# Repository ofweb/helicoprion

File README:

# Helicoprion Keyboard

The Helicoprion Keyboard is a 52-key diodeless, flippable, choc spaced, hotswap, aggressive column staggered, split keyboard powered by Pro Micro pin compatible board, eg a nice!nano or a KB2040.
It does not support wireless controllers, but you can use a nice!nano wired if you want

# Inspiration

* [Sweep](https://github.com/davidphilipbarr/Sweep) The main inspiration is from the ferris sweep I started trying to used I needed more keys.
* [Hillside](https://github.com/mmccoyd/hillside) The very pretty promicro foot print and how to wire it.
* [Torn](https://github.com/rtitmuss/torn) For not be afraid of showing th components and that look can be very sexy.

## Features

* Pro Micro MCU - Many options
* Sweep inspired layout - Ergonomic strong column staggering for short pinkies.
* Extra pinky column - for those not too often used keys.
* Flippable PCBs - Cheaper to order the PCBs
* Hotswap low profile choc switches - Experiment with different key switches with the hotswap sockets.
* Very large thumb cluster - Let your thumb do more of the work.
* Both SMD and THT diodes - Pick if you want the easier to solder or the smaller diodes.

## Bill of Materials (BOM)

Quantity | Item
--- | ---
2 | Helicoprion PCB
2 | Pro Micro pin compatable comtrollers
52 | Kailh choc v1 PG1350 switches
52 | Choc v1 keycaps
2 | TRRS jack PJ-320A (not needed for nice!nano)
1 | 3.5mm TRRS cable (not needed for nice!nano)
52 | Kahli hotswap sockets for choc v1 PG1350
4 | Pin headers (20 pin) or sockets
2 | Reset Button (optional) ALPS SKHLLCA010 or footprint compatible

## External footprints and symbols used

External symbols and footprints are not covered by the LICENSE in this repo.

* [Keebio-Parts.pretty](https://github.com/keebio/Keebio-Parts.pretty) is licensed under the MIT License.
* [keyswitches.pretty](https://github.com/daprice/keyswitches.pretty) is licensed under the Creative Commons Attribution-ShareAlike 4.0 International License.
* [Hillside](https://github.com/mmccoyd/hillside) is licensed under the MIT License.

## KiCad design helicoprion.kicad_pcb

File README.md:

# Helicoprion Keyboard

The Helicoprion Keyboard is a 44-key diodeless, flippable, choc spaced, hotswap, aggressive column staggered, split keyboard powered by Pro Micro pin compatible board, eg a nice!nano or a KB2040.
It does not have battery support, but you can use a nice!nano wired if you want.

I made this after having build and attempted to use a sweep. Tha lack of dedicated modifier keys kept being a problem for me. The normal tucky thumb keys are hard to reach for me so I came up with this that I think feels better.
I don't expect this to by my last iteration on a keyboard so it is made to allow me to recycle the MCU and the switches in a next iteration.

# Testing
If you want to see if this is right for you you can start with printing a paper tester (TODO). If you have access to a 3d-printer you can print the step file(TODO) from the repo and add you switches, this should give you a better indication on if it is right.

# Inspiration

* [Sweep](https://github.com/davidphilipbarr/Sweep) The main inspiration is from the ferris sweep I started trying to used I needed more keys.
* [Hillside](https://github.com/mmccoyd/hillside) The very pretty promicro foot print and how to wire it.
* [Torn](https://github.com/rtitmuss/torn) For not be afraid of showing the components and that it can look very nice.

## Features

* Pro Micro MCU - Many options
* Sweep inspired layout - Ergonomic strong column staggering for short pinkies.
* Flippable PCBs - Cheaper to order the PCBs
* Hotswap low profile choc switches - Experiment with different key switches with the hotswap sockets.
* Very large thumb cluster - Let your thumb do more of the work.
* Both SMD and THT diodes - Pick if you want the easier to solder or the smaller diodes.

## Bill of Materials (BOM)

[Interactive](https://ofweb.github.io/helicoprion/)

Quantity | Item
--- | ---
2 | Helicoprion PCB
2 | Pro Micro pin compatable comtrollers
44 | Kailh choc v1 PG1350 switches
44 | Choc v1 keycaps
44 | Kahli hotswap sockets for choc v1 PG1350
44 | Diodes both through-hole (eg. 1N4148) and smd (SOD-123) are supported
2 | TRRS jack PJ-320A (not needed for nice!nano)
1 | 3.5mm TRRS cable (not needed for nice!nano)
4 | Pin headers (20 pin) or sockets
2 | Reset Button (optional) ALPS SKHLLCA010 or footprint compatible

# releases
## V1
### Errata: 
 - sw9 connect pin 1 (square) to MCU pin 20 (row1)
 - sw10 connect pin 1 (square) to MCU pin 19 (row2)
 - MCU pin 10 to (col3) to MCU pin 10 (col3). The inner most pin is connected the outer most is not and need to be if you are using it.

# schematic

## External footprints and symbols used

External symbols and footprints are not covered by the LICENSE in this repo.

* [Keebio-Parts.pretty](https://github.com/keebio/Keebio-Parts.pretty) is licensed under the MIT License.
* [keyswitches.pretty](https://github.com/daprice/keyswitches.pretty) is licensed under the Creative Commons Attribution-ShareAlike 4.0 International License.
* [Hillside](https://github.com/mmccoyd/hillside) is licensed under the MIT License.

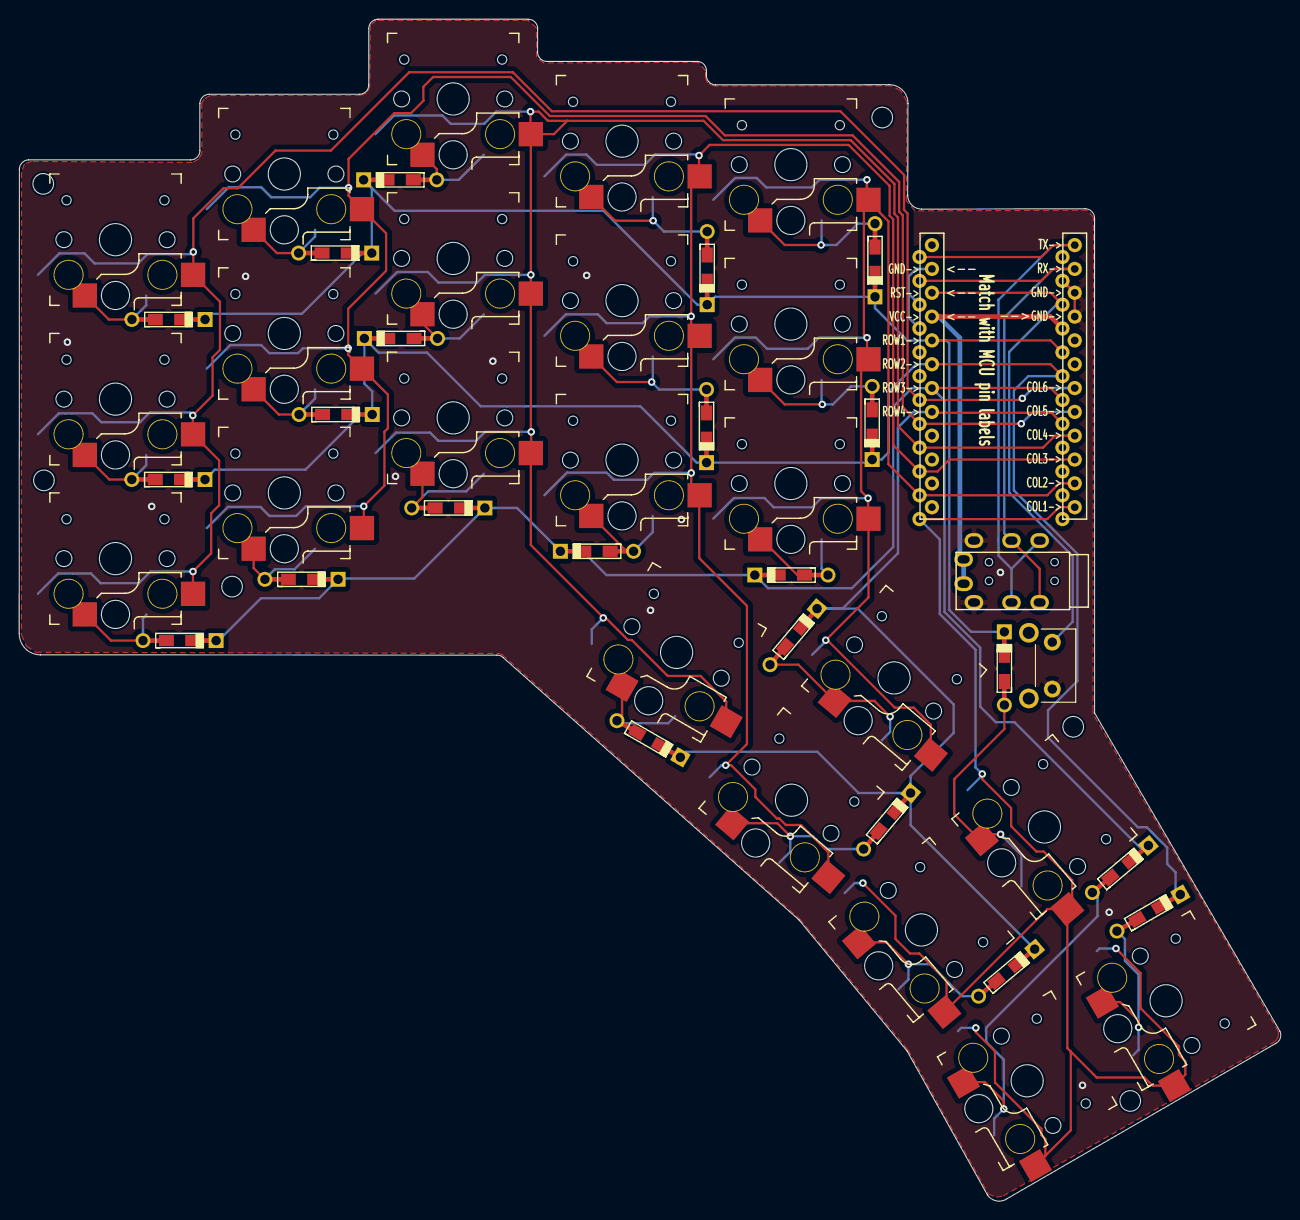
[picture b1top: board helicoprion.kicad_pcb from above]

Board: 2 copper layers, 134.5 x 126.0 mm, 54 parts (1 on the bottom side), 37 nets.

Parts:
D1, D2, D3, D4, D5, D6, D7, D9, D10, D11, D12, D13, D14, D15, D16, D17, D18, D19, D20, D21, D22, D23: 1N4148; Diode-dual
H1, H2, H3, H4, H5, H6: MountingHole; MountingHole_2.2mm_M2
J1, J2: TRRS; TRRS-PJ-320A
RSW1: SW_Push; SW_SKHLLCA010
SW1, SW2, SW3, SW4, SW5, SW6, SW7, SW9, SW10, SW11, SW12, SW13, SW14, SW15, SW16, SW17, SW18, SW19, SW20, SW21, SW22, SW23: SW_SPST; Kailh_socket_PG1350_reversible
U1: ProMicro_r; ProMicro_v2

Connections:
+3.3V: J1.1 (Sleeve), J2.1 (Sleeve), U1.21 (VCC)
GND: J1.2 (tip), J2.2 (tip), RSW1.1, U1.3 (GND), U1.4 (GND), U1.23 (GND)
unnamed: D1.2 (A), SW1.1 (A)
unnamed: D2.2 (A), SW2.1 (A)
unnamed: D3.2 (A), SW5.1 (A)
unnamed: D4.2 (A), SW7.1 (A)
unnamed: D5.2 (A), SW6.1 (A)
unnamed: D6.2 (A), SW3.1 (A)
unnamed: D7.2 (A), SW4.1 (A)
unnamed: D9.2 (A), SW9.1 (A)
unnamed: D10.2 (A), SW10.1 (A)
unnamed: D11.2 (A), SW11.1 (A)
unnamed: D12.2 (A), SW12.1 (A)
unnamed: D13.2 (A), SW13.1 (A)
unnamed: D14.2 (A), SW14.1 (A)
unnamed: D15.2 (A), SW15.1 (A)
unnamed: D16.2 (A), SW16.1 (A)
unnamed: D17.2 (A), SW17.1 (A)
unnamed: D18.2 (A), SW18.1 (A)
unnamed: D19.2 (A), SW19.1 (A)
unnamed: D20.2 (A), SW20.1 (A)
unnamed: D21.2 (A), SW21.1 (A)
unnamed: D22.2 (A), SW22.1 (A)
unnamed: D23.2 (A), SW23.1 (A)
col1: SW4.2 (B), SW5.2 (B), SW6.2 (B), SW7.2 (B), U1.12 (B5/9)
col2: SW3.2 (B), SW9.2 (B), SW10.2 (B), SW11.2 (B), U1.11 (B4/8)
col3: SW2.2 (B), SW12.2 (B), SW13.2 (B), SW14.2 (B), U1.10 (E6/7)
col4: SW1.2 (B), SW15.2 (B), SW16.2 (B), SW17.2 (B), U1.9 (D7/6)
col5: SW18.2 (B), SW19.2 (B), SW20.2 (B), U1.8 (C6/5)
col6: SW21.2 (B), SW22.2 (B), SW23.2 (B), U1.7 (D4/4)
reset: RSW1.2, U1.22 (RST)
row1: D3.1 (K), D9.1 (K), D12.1 (K), D15.1 (K), D18.1 (K), D21.1 (K), U1.20 (A3/F4)
row2: D4.1 (K), D10.1 (K), D13.1 (K), D16.1 (K), D19.1 (K), D22.1 (K), U1.19 (A2/F5)
row3: D5.1 (K), D11.1 (K), D14.1 (K), D17.1 (K), D20.1 (K), D23.1 (K), U1.18 (A1/F6)
row4: D1.1 (K), D2.1 (K), D6.1 (K), D7.1 (K), U1.17 (A0/F7)
rx: J1.4 (Ring2), J2.3 (Ring1), U1.2 (D2/RX1)
tx: J1.3 (Ring1), J2.4 (Ring2), U1.1 (D3/TX0)

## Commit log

2023-04-19 add images and fix edge cut
2023-04-20 readme in markdown
2023-04-20 rename kicad files
2023-04-20 added 3d models
2023-04-27 finish layout
2023-04-27 addded gerber
2023-04-27 Add ground vias and gerber
2023-04-28 fix silkscreen for mcu
2023-05-12 start of firmware and interactive bom
2023-05-12 add link to bom
2023-05-12 move ibom to root
2023-05-12 fix interactive link
2023-07-03 new gerber and ibom
2023-08-16 fix erata for v1 and get left side working
2023-08-16 update readme, bom and 3d renders
2023-08-16 move errata into readme
2023-08-16 typo fixes
2023-08-16 remove v1 gerber as it should not be ordered. move new ibom to root
2023-08-30 colemak mdh
